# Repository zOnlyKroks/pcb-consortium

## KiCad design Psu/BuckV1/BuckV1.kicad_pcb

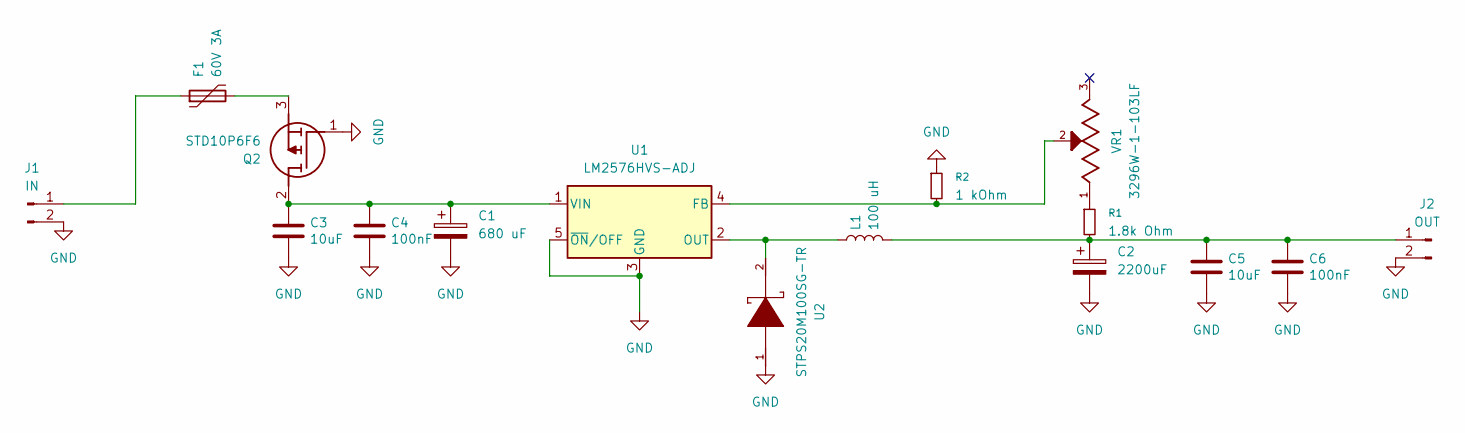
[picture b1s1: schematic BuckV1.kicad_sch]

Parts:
C1: 680 uF; CP_Radial_D12.5mm_P5.00mm; LCSC Part # C233101
C2: 2200uF; CP_Radial_D16.0mm_P7.50mm; LCSC Part # C49256808
C3, C5: 10uF; C_0603_1608Metric; LCSC C19702
C4, C6: 100nF; C_0603_1608Metric; LCSC C14663
F1: 60V 3A; Polyfuse_60R300XF; LCSC Part # C207120
J1: IN; PinHeader_1x02_P2.54mm_Vertical; LCSC Part # C492401
J2: OUT; PinHeader_1x02_P2.54mm_Vertical; LCSC Part # C492401
L1: 100 uH; L_12x12mm_H8mm; LCSC Part # C5368704
Q2: STD10P6F6; Mouser Part Number 511-STD10P6F6
R1: 1.8k Ohm; R_0805_2012Metric; LCSC Part # C17398
R2: 1 kOhm; R_0805_2012Metric; LCSC Part # C95781
U1: LM2576HVS-ADJ; TO-263-5_TabPin3; LCSC Part # C18212635
U2: STPS20M100SG-TR; MANUFACTURER_PART_NUMBER STPS20M100SGTR; LCSC Part # C969989
VR1: 3296W-1-103LF; TRIM_3296W-1-103LF; PARTREV 05/16; LCSC Part # C49190453

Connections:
GND: C1.2, C2.2, C3.2, C4.2, C5.2, C6.2, J1.2, J2.2, Q2.1 (G), R2.1, U1.3 (GND), U1.5 (~ON/OFF), U2.1
unnamed: F1.1, J1.1
unnamed: C2.1, C5.1, C6.1, J2.1, L1.2, R1.2
unnamed: C1.1, C3.1, C4.1, Q2.2 (D), U1.1 (VIN)
unnamed: F1.2, Q2.3 (S)
unnamed: R1.1, VR1.1
unnamed: R2.2, U1.4 (FB), VR1.2
unnamed: L1.1, U1.2 (OUT), U2.2

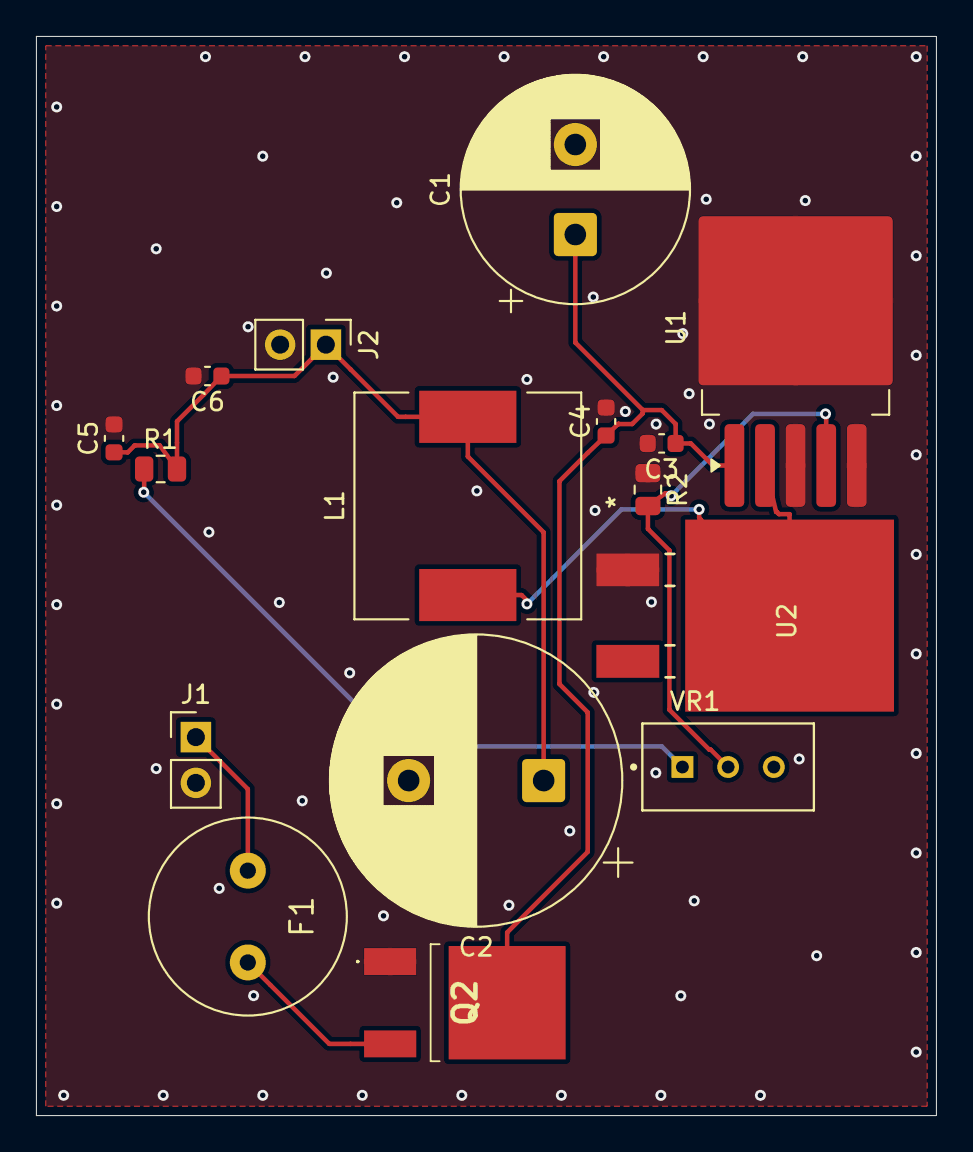
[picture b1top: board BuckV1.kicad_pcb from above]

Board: 2 copper layers, 50.0 x 59.9 mm, 16 parts (0 on the bottom side), 8 nets.

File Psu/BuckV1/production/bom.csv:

Designator,Footprint,Quantity,Value,LCSC Part #
C1,CP_Radial_D12.5mm_P5.00mm,1,680 uF,C233101
C2,CP_Radial_D16.0mm_P7.50mm,1,2200uF,C49256808
"C3, C5",0603,2,10uF,C19702
"C4, C6",0603,2,100nF,C14663
F1,Polyfuse_60R300XF,1,60V 3A,C207120
J1,PinHeader_1x02_P2.54mm_Vertical,1,IN,C492401
J2,PinHeader_1x02_P2.54mm_Vertical,1,OUT,C492401
L1,L_12x12mm_H8mm,1,100 uH,C5368704
Q2,STD10P6F6,1,STD10P6F6,C457501
R1,0805,1,1.8k Ohm,C17398
R2,0805,1,1 kOhm,C95781
U1,TO-263-5_TabPin3,1,LM2576HVS-ADJ,C18212635
U2,STPS20M100SG-TR,1,STPS20M100SG-TR,C969989
VR1,TRIM_3296W-1-103LF,1,3296W-1-103LF,C49190453

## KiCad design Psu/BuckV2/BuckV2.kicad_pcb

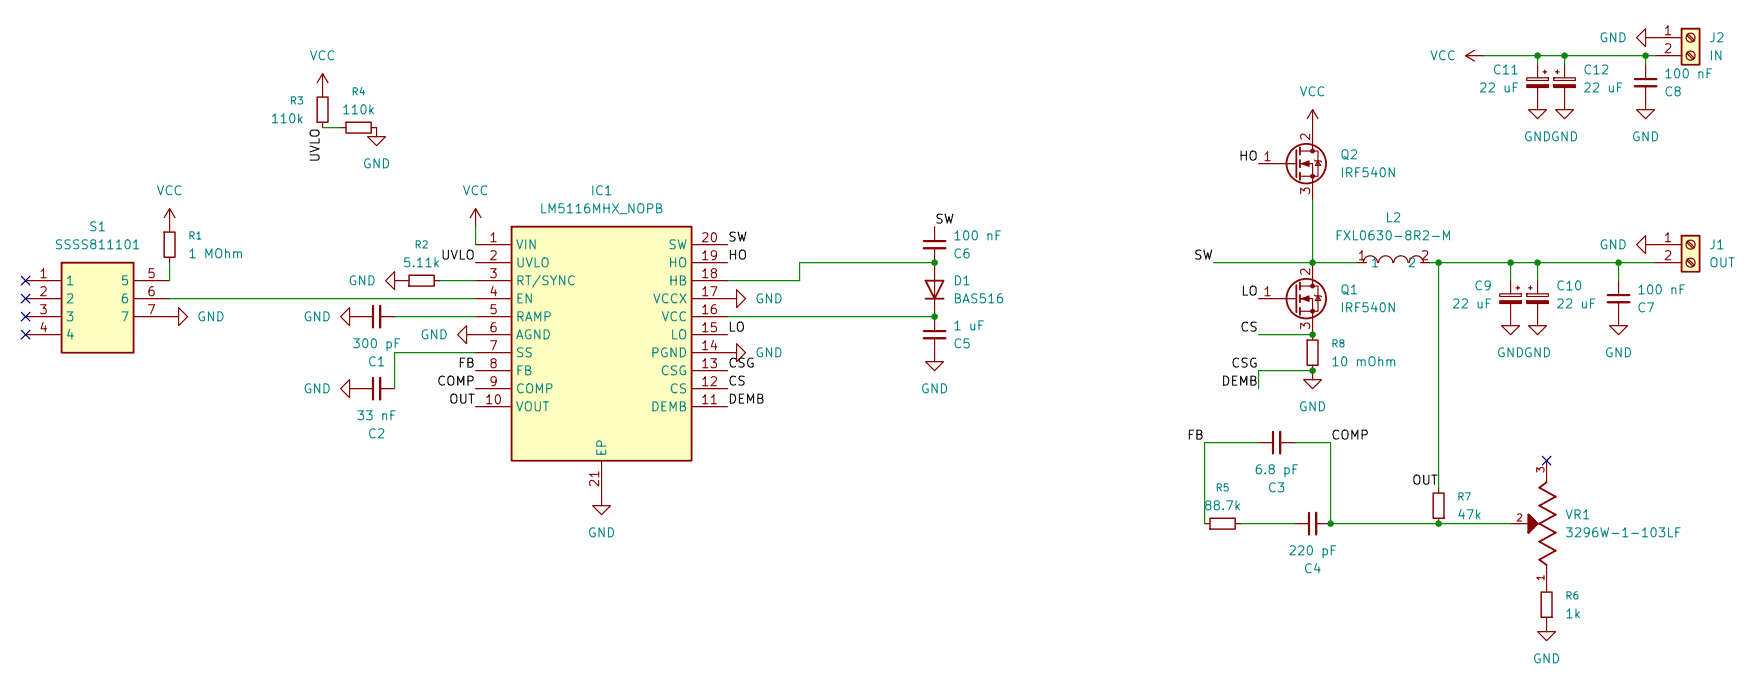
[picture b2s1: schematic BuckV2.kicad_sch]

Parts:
C1: 300 pF; C_0603_1608Metric
C2: 33 nF; C_0603_1608Metric
C3: 6.8 pF; C_0603_1608Metric
C4: 220 pF; C_0603_1608Metric
C5: 1 uF; C_0603_1608Metric
C6, C7, C8: 100 nF; C_0603_1608Metric
C9, C10, C11, C12: 22 uF; CP_Radial_D10.0mm_P5.00mm
D1: BAS516; D_SOD-523
IC1: LM5116MHX_NOPB; SOP65P640X110-21N; Mouser Part Number 926-LM5116MHX/NOPB
J1: OUT; WJ500V-5.08-2P
J2: IN; WJ500V-5.08-2P
L2: FXL0630-8R2-M; IND-SMD_L7.0-W6.6_FXL0630; MPN FXL0630-8R2-M; LCSC Part C167222
Q1, Q2: IRF540N; TO-220-3_Vertical
R1: 1 MOhm; R_0603_1608Metric
R2: 5.11k; R_0603_1608Metric
R3, R4: 110k; R_0603_1608Metric
R5: 88.7k; R_0603_1608Metric
R6: 1k; R_0603_1608Metric
R7: 47k; R_0603_1608Metric
R8: 10 mOhm; R_0603_1608Metric
S1: SSSS811101; Mouser Part Number 688-SSSS811101
VR1: 3296W-1-103LF; TRIM_3296W-1-103LF; PARTREV 05/16

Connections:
/COMP: C3.2, C4.2, IC1.9 (COMP), R7.1, VR1.2
/CS: IC1.12 (CS), Q1.3 (S), R8.1
/FB: C3.1, IC1.8 (FB), R5.1
/HO: IC1.19 (HO), Q2.1 (G)
/LO: IC1.15 (LO), Q1.1 (G)
/OUT: C7.1, C9.1, C10.1, IC1.10 (VOUT), J1.2, L2.2, R7.2
/SW: C6.1, IC1.20 (SW), L2.1, Q1.2 (D), Q2.3 (S)
/UVLO: IC1.2 (UVLO), R3.1, R4.1
GND: C1.1, C2.1, C5.2, C7.2, C8.2, C9.2, C10.2, C11.2, C12.2, IC1.6 (AGND), IC1.11 (DEMB), IC1.13 (CSG), IC1.14 (PGND), IC1.17 (VCCX), IC1.21 (EP), J1.1, J2.1, R2.1, R4.2, R6.1, R8.2, S1.7
unnamed: C4.1, R5.2
unnamed: C6.2, D1.2 (A), IC1.18 (HB)
unnamed: C5.1, D1.1 (K), IC1.16 (VCC)
unnamed: IC1.4 (EN), S1.6
unnamed: C1.2, IC1.5 (RAMP)
unnamed: IC1.3 (RT/SYNC), R2.2
unnamed: C2.2, IC1.7 (SS)
unnamed: R1.2, S1.5
unnamed: R6.2, VR1.1
VCC: C8.1, C11.1, C12.1, IC1.1 (VIN), J2.2, Q2.2 (D), R1.1, R3.2

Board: 2 copper layers, 29 parts (0 on the bottom side), 19 nets, no tracks yet.

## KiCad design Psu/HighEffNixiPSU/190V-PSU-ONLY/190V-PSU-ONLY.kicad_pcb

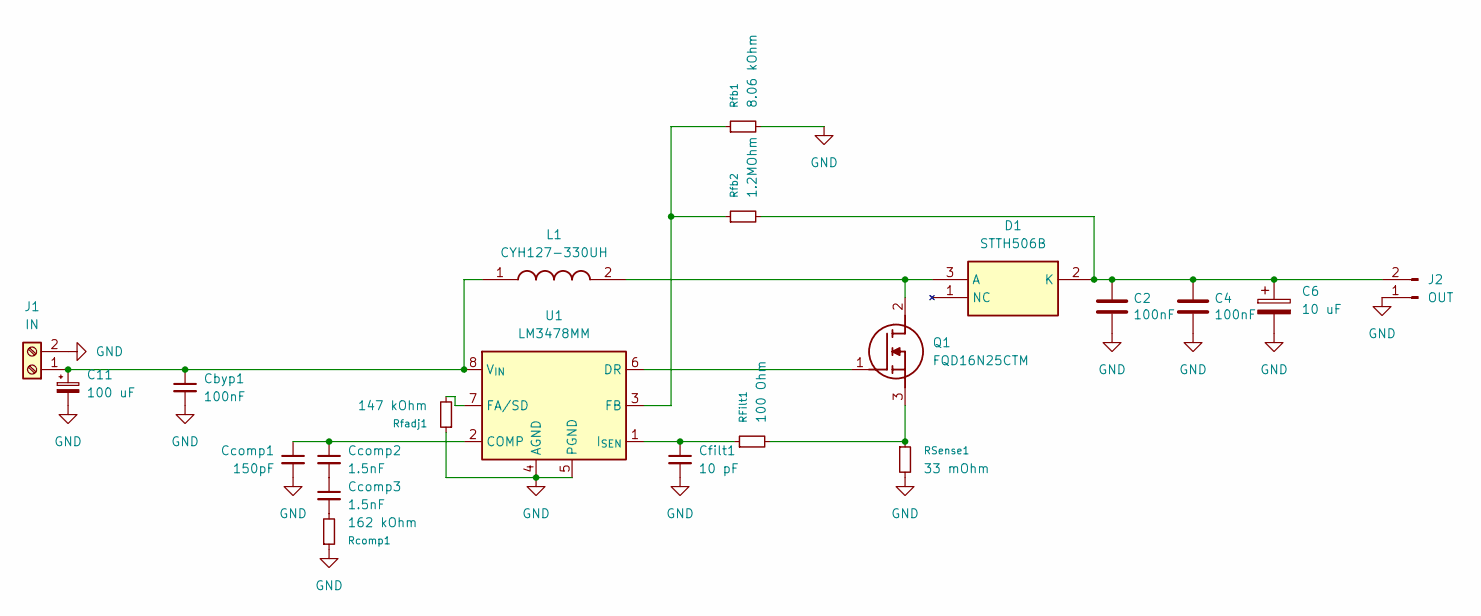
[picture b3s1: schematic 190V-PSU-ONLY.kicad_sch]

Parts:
C2, C4: 100nF; C_1206_3216Metric; LCSC C365814
C6: 10 uF; C_Elec_10x10.2; LCSC Part # C48970948
C11: 100 uF; CP_EIA-3216-18_Kemet-A
Cbyp1: 100nF; C_0805_2012Metric; LCSC Part # C28233
Ccomp1: 150pF; C_0805_2012Metric; LCSC Part # C1716
Ccomp2, Ccomp3: 1.5nF; C_0805_2012Metric; LCSC Part # C1717
Cfilt1: 10 pF; C_0805_2012Metric; LCSC Part # C107107
D1: STTH506B; STTH506BTR; Mouser Part Number 511-STTH506B-TR
J1: IN; WJ500V-5.08-2P
J2: OUT; PinHeader_1x02_P2.54mm_Horizontal
L1: CYH127-330UH; Mouser Part Number 652-SDR1307-331KL
Q1: FQD16N25CTM; Mouser Part Number 512-FQD16N25CTM
RFilt1: 100 Ohm; R_0805_2012Metric; LCSC Part # C17408
RSense1: 33 mOhm; R_1210_3225Metric; LCSC Part # C723419
Rcomp1: 162 kOhm; R_0805_2012Metric; LCSC Part # C47115899
Rfadj1: 147 kOhm; R_0805_2012Metric; LCSC Part # C47115874
Rfb1: 8.06 kOhm; R_0805_2012Metric; LCSC Part # C857074
Rfb2: 1.2MOhm; R_1206_3216Metric; LCSC Part # C36337
U1: LM3478MM; VSSOP-8_3x3mm_P0.65mm; LCSC Part # C9404

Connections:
GND: C2.2, C4.2, C6.2, C11.2, Cbyp1.2, Ccomp1.2, Cfilt1.2, J1.2, J2.1, RSense1.2, Rcomp1.1, Rfadj1.1, Rfb1.2, U1.4 (AGND), U1.5 (PGND)
unnamed: Ccomp2.2, Ccomp3.1
unnamed: Ccomp3.2, Rcomp1.2
unnamed: D1.3 (A), L1.2, Q1.2 (D)
unnamed: C2.1, C4.1, C6.1, D1.2 (K), J2.2, Rfb2.2
unnamed: C11.1, Cbyp1.1, J1.1, L1.1, U1.8 (V_{IN})
unnamed: Q1.1 (G), U1.6 (DR)
unnamed: Q1.3 (S), RFilt1.2, RSense1.1
unnamed: Ccomp1.1, Ccomp2.1, U1.2 (COMP)
unnamed: Rfadj1.2, U1.7 (FA/SD)
unnamed: Rfb1.1, Rfb2.1, U1.3 (FB)
unnamed: Cfilt1.1, RFilt1.1, U1.1 (I_{SEN})

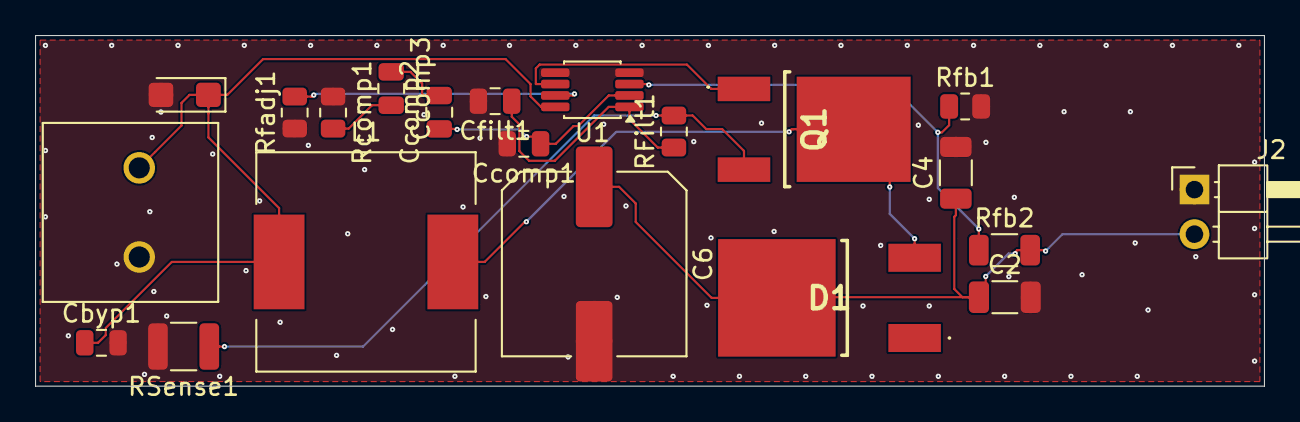
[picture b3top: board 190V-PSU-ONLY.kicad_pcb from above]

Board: 2 copper layers, 70.0 x 20.0 mm, 21 parts (0 on the bottom side), 12 nets.

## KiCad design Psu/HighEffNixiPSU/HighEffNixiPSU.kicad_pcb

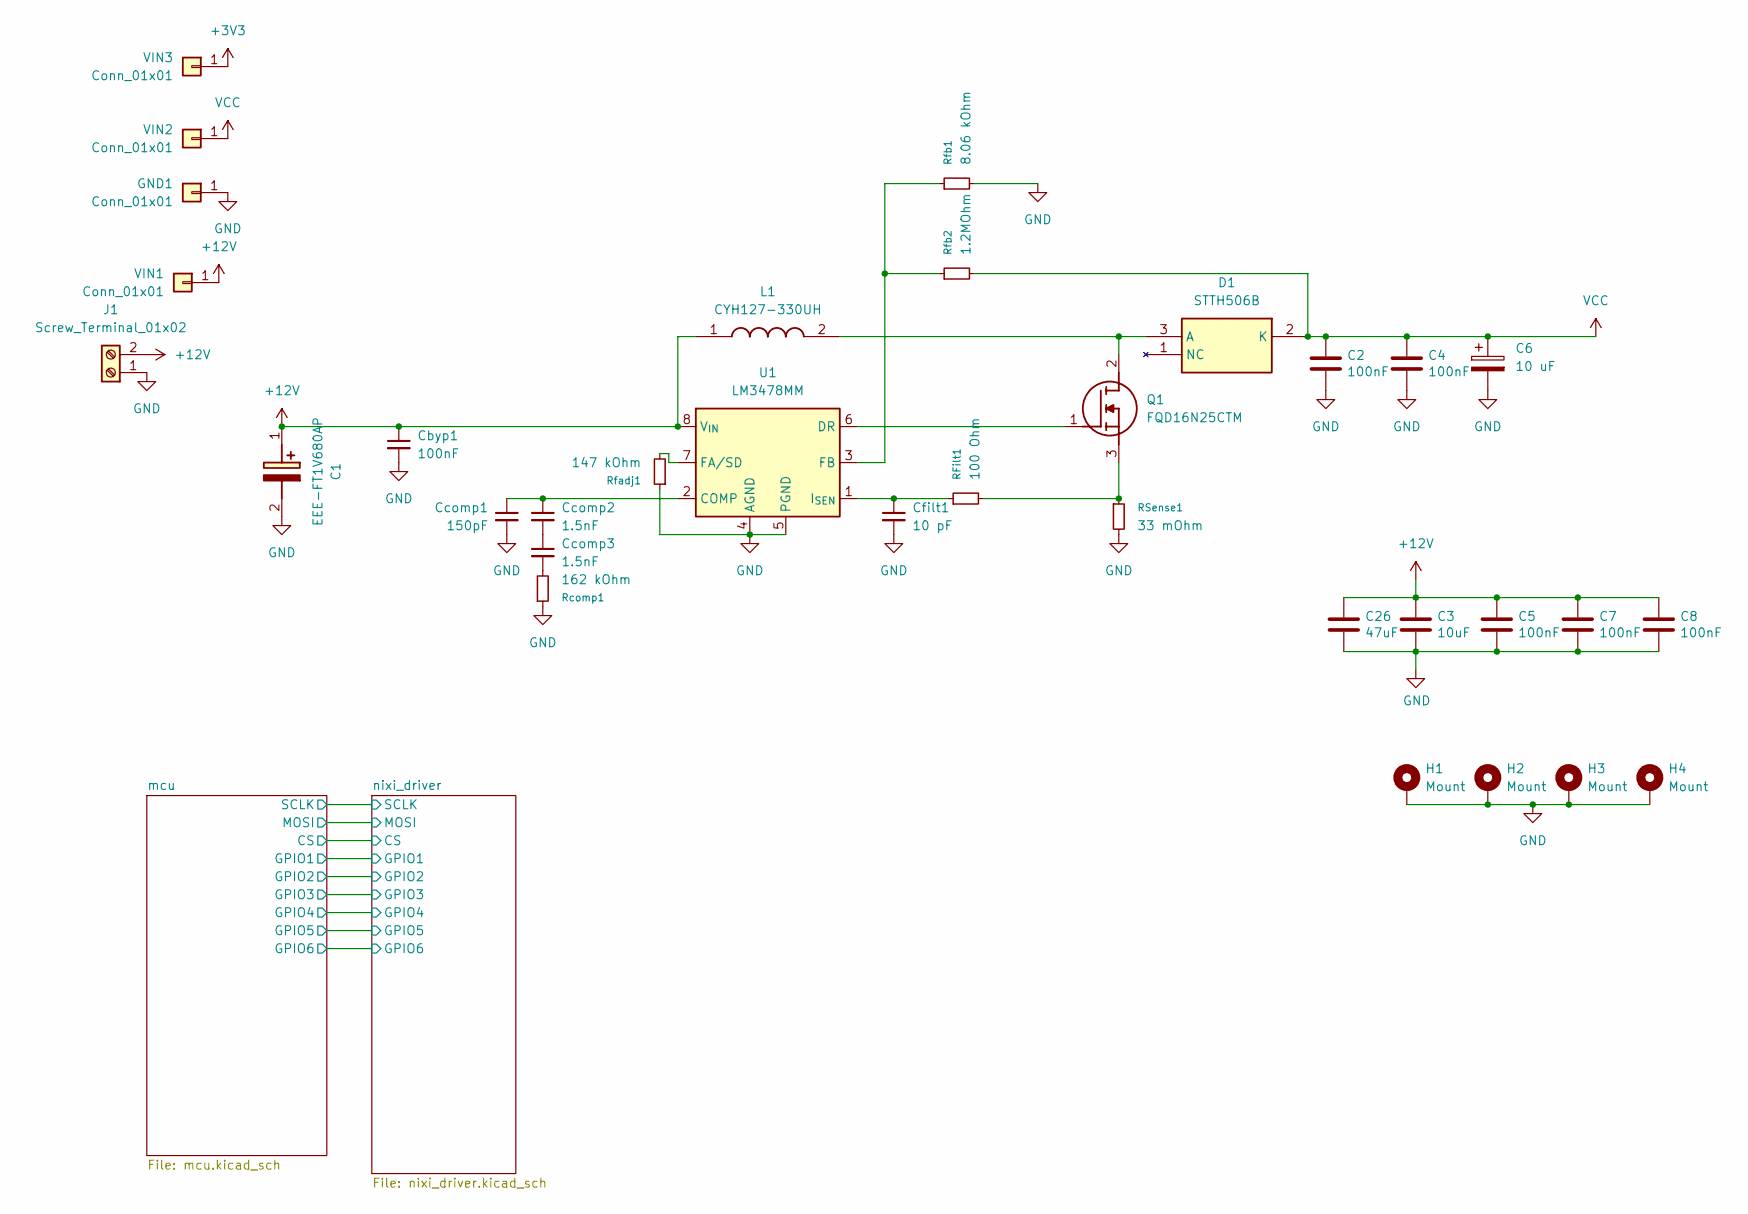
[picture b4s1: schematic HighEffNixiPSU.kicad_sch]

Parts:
C1: EEE-FT1V680AP; EEE1AA101SP; Mouser Part Number 667-EEE-FT1V680AP
C2, C4: 100nF; C_1206_3216Metric; LCSC C365814
C3: 10uF; C_0603_1608Metric; LCSC C1691
C5, C7, C8: 100nF; C_0603_1608Metric; LCSC C14663
C6: 10 uF; C_Elec_10x10.2; LCSC Part # C48970948
C26: 47uF; C_1206_3216Metric; LCSC C96123
Cbyp1: 100nF; C_0805_2012Metric; LCSC Part # C28233
Ccomp1: 150pF; C_0805_2012Metric; LCSC Part # C1716
Ccomp2, Ccomp3: 1.5nF; C_0805_2012Metric; LCSC Part # C1717
Cfilt1: 10 pF; C_0805_2012Metric; LCSC Part # C107107
D1: STTH506B; STTH506BTR; Mouser Part Number 511-STTH506B-TR
GND1: Conn_01x01; PinHeader_1x01_P2.54mm_Vertical; LCSC Part # C492400
H1, H2, H3, H4: Mount; MountingHole_3mm_Pad_TopOnly
J1: Screw_Terminal_01x02; WJ500V-5.08-2P
L1: CYH127-330UH; Mouser Part Number 652-SDR1307-331KL
Q1: FQD16N25CTM; Mouser Part Number 512-FQD16N25CTM
RFilt1: 100 Ohm; R_0805_2012Metric; LCSC Part # C17408
RSense1: 33 mOhm; R_1210_3225Metric; LCSC Part # C723419
Rcomp1: 162 kOhm; R_0805_2012Metric; LCSC Part # C47115899
Rfadj1: 147 kOhm; R_0805_2012Metric; LCSC Part # C47115874
Rfb1: 8.06 kOhm; R_0805_2012Metric; LCSC Part # C857074
Rfb2: 1.2MOhm; R_1206_3216Metric; LCSC Part # C36337
U1: LM3478MM; VSSOP-8_3x3mm_P0.65mm; LCSC Part # C9404
VIN1, VIN2, VIN3: Conn_01x01; PinHeader_1x01_P2.54mm_Vertical; LCSC Part # C492400

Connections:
+3V3: VIN3.1 (Pin_1_1); also elsewhere on the board
+12V: C1.1 (+), C3.1, C5.1, C7.1, C8.1, C26.1, Cbyp1.1, J1.2, L1.1, U1.8 (V_{IN}), VIN1.1 (Pin_1_1); also elsewhere on the board
GND: C1.2 (-), C2.2, C3.2, C4.2, C5.2, C6.2, C7.2, C8.2, C26.2, Cbyp1.2, Ccomp1.2, Cfilt1.2, GND1.1 (Pin_1_1), H1.1 (1_1), H2.1 (1_1), H3.1 (1_1), H4.1 (1_1), J1.1, RSense1.2, Rcomp1.1, Rfadj1.1, Rfb1.2, U1.4 (AGND), U1.5 (PGND); also elsewhere on the board
unnamed: Ccomp2.2, Ccomp3.1
unnamed: Ccomp3.2, Rcomp1.2
unnamed: D1.3 (A), L1.2, Q1.2 (D)
unnamed: Q1.1 (G), U1.6 (DR)
unnamed: Q1.3 (S), RFilt1.2, RSense1.1
unnamed: Ccomp1.1, Ccomp2.1, U1.2 (COMP)
unnamed: Rfadj1.2, U1.7 (FA/SD)
unnamed: Rfb1.1, Rfb2.1, U1.3 (FB)
unnamed: Cfilt1.1, RFilt1.1, U1.1 (I_{SEN})
VCC: C2.1, C4.1, C6.1, D1.2 (K), Rfb2.2, VIN2.1 (Pin_1_1); also elsewhere on the board

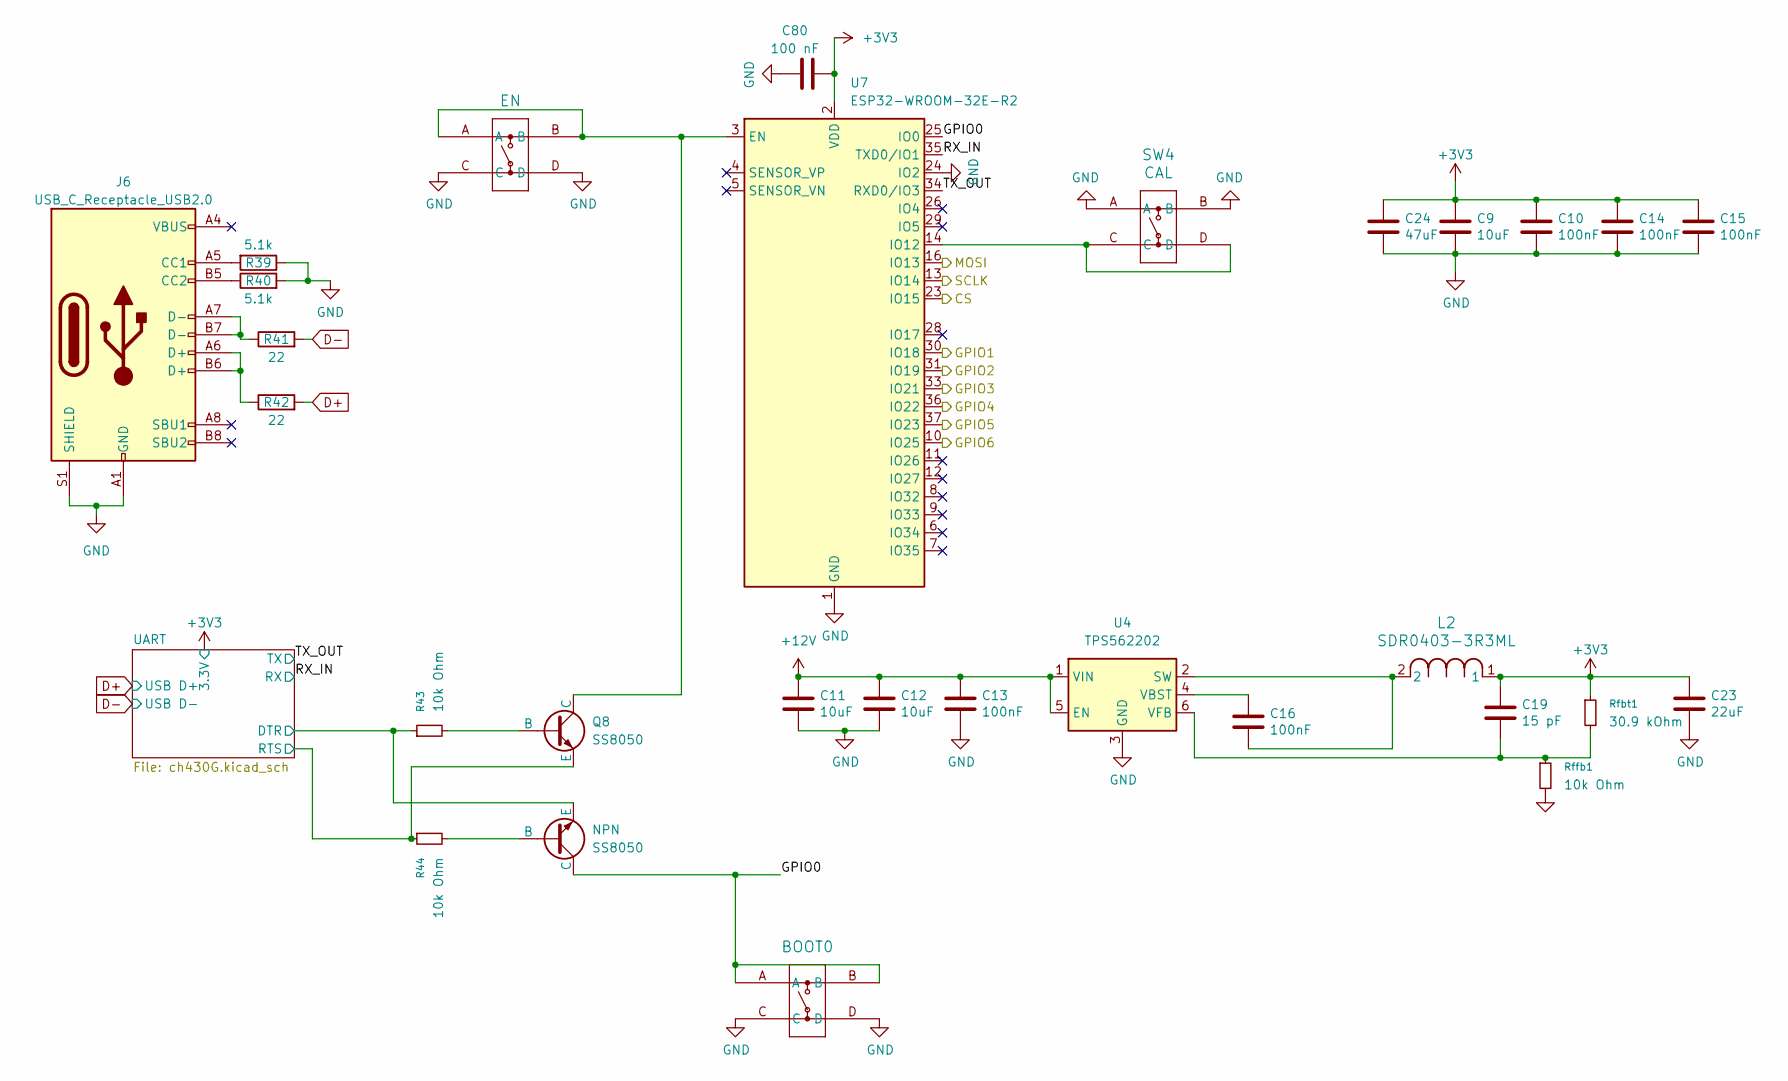
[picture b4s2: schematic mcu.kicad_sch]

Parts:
C9: 10uF; C_0603_1608Metric; LCSC C1691
C10, C13, C14, C15, C16: 100nF; C_0603_1608Metric; LCSC C14663
C11, C12: 10uF; C_0603_1608Metric; LCSC C92487
C19: 15 pF; R_0805_2012Metric; LCSC C107110
C23: 22uF; C_0805_2012Metric; LCSC C45783
C24: 47uF; C_1206_3216Metric; LCSC C96123
C80: 100 nF; C_0805_2012Metric; LCSC Part # C49678
J6: USB_C_Receptacle_USB2.0; USB_C_Receptacle_HRO_TYPE-C-31-M-12; JlcRotOffset 180
L2: SDR0403-3R3ML; IND_BOURNS_SDR0403; LCSC Part # C139481
Q8: SS8050; SOT-23; LCSC Part # C916392
R39, R40: 5.1k; R_0805_2012Metric; LCSC Part # C27834
R41, R42: 22; R_0805_2012Metric; LCSC Part # C17561
R43, R44: 10k Ohm; R_0805_2012Metric
Rfbt1: 30.9 kOhm; R_0603_1608Metric; LCSC Part # C2930090
Rffb1: 10k Ohm; R_0603_1608Metric; LCSC Part # C25804
SS8050: NPN; SOT-23; LCSC Part # C916392
SW3: EN; KH-6X6X5H-STM_SKE; LCSC Part # C2837531
SW4: CAL; KH-6X6X5H-STM_SKE; LCSC Part # C2837531
SW5: BOOT0; KH-6X6X5H-STM_SKE; LCSC Part # C2837531
U4: TPS562202; SOT-563; LCSC Part # C2877547
U7: ESP32-WROOM-32E-R2; ESP32-WROOM-32D

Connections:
+3V3: C9.1, C10.1, C14.1, C15.1, C19.1, C23.1, C24.1, C80.1, L2.1, Rfbt1.1, U7.2 (VDD); also elsewhere on the board
+12V: C11.1, C12.1, C13.1, U4.1 (VIN), U4.5 (EN); also elsewhere on the board
/mcu/CS: U7.23 (IO15); also elsewhere on the board
/mcu/GPIO0: SS8050.1 (C), SW5.A, SW5.B, U7.25 (IO0)
/mcu/GPIO1: U7.30 (IO18); also elsewhere on the board
/mcu/GPIO2: U7.31 (IO19); also elsewhere on the board
/mcu/GPIO3: U7.33 (IO21); also elsewhere on the board
/mcu/GPIO4: U7.36 (IO22); also elsewhere on the board
/mcu/GPIO5: U7.37 (IO23); also elsewhere on the board
/mcu/GPIO6: U7.10 (IO25); also elsewhere on the board
/mcu/MOSI: U7.16 (IO13); also elsewhere on the board
/mcu/RX_IN: U7.35 (TXD0/IO1); also elsewhere on the board
/mcu/SCLK: U7.13 (IO14); also elsewhere on the board
/mcu/TX_OUT: U7.34 (RXD0/IO3); also elsewhere on the board
/mcu/UART/DTR: R43.1, SS8050.3 (E); also elsewhere on the board
/mcu/UART/RTS: Q8.3 (E), R44.1; also elsewhere on the board
D+: R42.2; also elsewhere on the board
D-: R41.2; also elsewhere on the board
GND: C9.2, C10.2, C11.2, C12.2, C13.2, C14.2, C15.2, C23.2, C24.2, C80.2, J6.A1 (GND), J6.A12 (GND), J6.B1 (GND), J6.B12 (GND), J6.S1 (SHIELD), R39.1, R40.2, Rffb1.2, SW3.C, SW3.D, SW4.A, SW4.B, SW5.C, SW5.D, U4.3 (GND), U7.1 (GND), U7.15 (GND), U7.24 (IO2), U7.38 (GND), U7.39 (GND); also elsewhere on the board
unnamed: J6.A5 (CC1), R39.2
unnamed: J6.B5 (CC2), R40.1
unnamed: J6.A6 (D+), J6.B6 (D+), R42.1
unnamed: J6.A7 (D-), J6.B7 (D-), R41.1
unnamed: Q8.2 (B), R43.2
unnamed: Q8.1 (C), SW3.A, SW3.B, U7.3 (EN)
unnamed: R44.2, SS8050.2 (B)
unnamed: C16.2, L2.2, U4.2 (SW)
unnamed: C16.1, U4.4 (VBST)
unnamed: C19.2, Rfbt1.2, Rffb1.1, U4.6 (VFB)
unnamed: SW4.C, SW4.D, U7.14 (IO12)

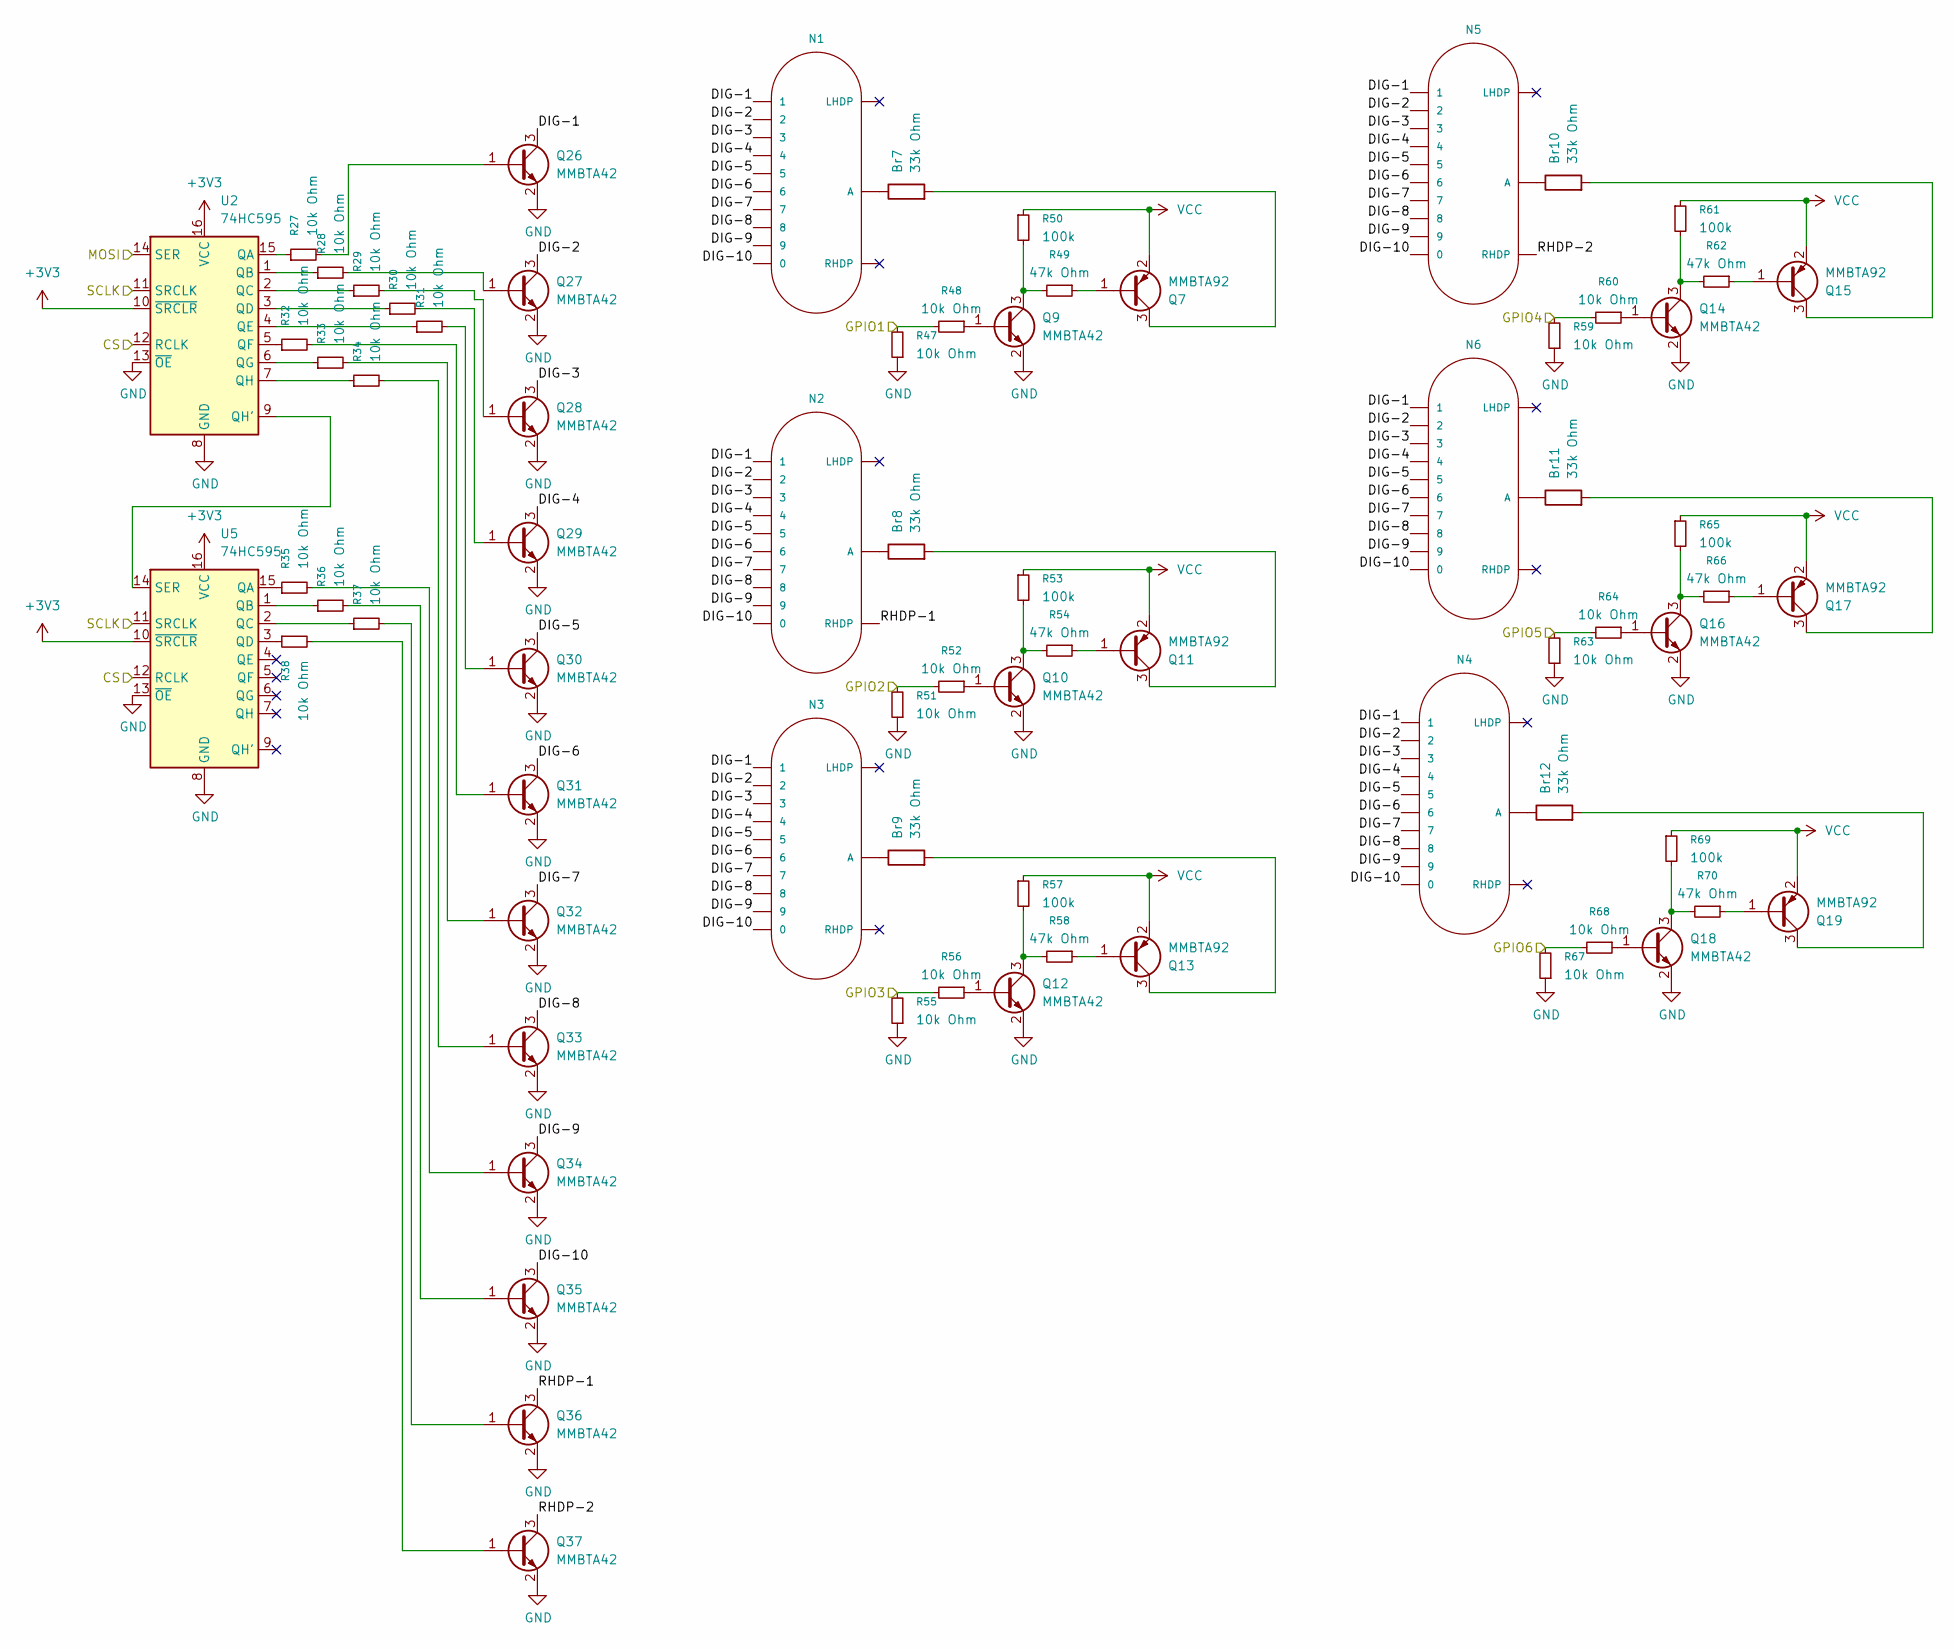
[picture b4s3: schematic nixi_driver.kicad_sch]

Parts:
Br7, Br8, Br9, Br10, Br11, Br12: 33k Ohm; R_0805_2012Metric; LCSC Part # C17633
N1, N2, N3, N4, N5, N6: IN-16; nixies-us-IN-16
Q7, Q11, Q13, Q15, Q17, Q19: MMBTA92; SOT-23
Q9, Q10, Q12, Q14, Q16, Q18, Q26, Q27, Q28, Q29, Q30, Q31, Q32, Q33, Q34, Q35, Q36, Q37: MMBTA42; SOT-23
R27, R28, R29, R30, R31, R32, R33, R34, R35, R36, R37, R38, R47, R48, R51, R52, R55, R56, R59, R60, R63, R64, R67, R68: 10k Ohm; R_0603_1608Metric; LCSC Part # C25804
R49, R54, R58, R62, R66, R70: 47k Ohm; R_0603_1608Metric; LCSC Part # C25804
R50, R53, R57, R61, R65, R69: 100k; R_0603_1608Metric; LCSC Part # C25804
U2, U5: 74HC595; SOIC-16_3.9x9.9mm_P1.27mm; LCSC Part # C10092

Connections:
+3V3: U2.10 (~SRCLR), U2.16 (VCC), U5.10 (~SRCLR), U5.16 (VCC); also elsewhere on the board
/mcu/CS: U2.12 (RCLK), U5.12 (RCLK); also elsewhere on the board
/mcu/GPIO1: R47.2, R48.2; also elsewhere on the board
/mcu/GPIO2: R51.2, R52.2; also elsewhere on the board
/mcu/GPIO3: R55.2, R56.2; also elsewhere on the board
/mcu/GPIO4: R59.2, R60.2; also elsewhere on the board
/mcu/GPIO5: R63.2, R64.2; also elsewhere on the board
/mcu/GPIO6: R67.2, R68.2; also elsewhere on the board
/mcu/MOSI: U2.14 (SER); also elsewhere on the board
/mcu/SCLK: U2.11 (SRCLK), U5.11 (SRCLK); also elsewhere on the board
/nixi_driver/DIG-1: N1.1, N2.1, N3.1, N4.1, N5.1, N6.1, Q26.3 (C)
/nixi_driver/DIG-2: N1.2, N2.2, N3.2, N4.2, N5.2, N6.2, Q27.3 (C)
/nixi_driver/DIG-3: N1.3, N2.3, N3.3, N4.3, N5.3, N6.3, Q28.3 (C)
/nixi_driver/DIG-4: N1.4, N2.4, N3.4, N4.4, N5.4, N6.4, Q29.3 (C)
/nixi_driver/DIG-5: N1.5, N2.5, N3.5, N4.5, N5.5, N6.5, Q30.3 (C)
/nixi_driver/DIG-6: N1.6, N2.6, N3.6, N4.6, N5.6, N6.6, Q31.3 (C)
/nixi_driver/DIG-7: N1.7, N2.7, N3.7, N4.7, N5.7, N6.7, Q32.3 (C)
/nixi_driver/DIG-8: N1.8, N2.8, N3.8, N4.8, N5.8, N6.8, Q33.3 (C)
/nixi_driver/DIG-9: N1.9, N2.9, N3.9, N4.9, N5.9, N6.9, Q34.3 (C)
/nixi_driver/DIG-10: N1.0, N2.0, N3.0, N4.0, N5.0, N6.0, Q35.3 (C)
/nixi_driver/RHDP-1: N2.RHDP, Q36.3 (C)
/nixi_driver/RHDP-2: N5.RHDP, Q37.3 (C)
GND: Q9.2 (E), Q10.2 (E), Q12.2 (E), Q14.2 (E), Q16.2 (E), Q18.2 (E), Q26.2 (E), Q27.2 (E), Q28.2 (E), Q29.2 (E), Q30.2 (E), Q31.2 (E), Q32.2 (E), Q33.2 (E), Q34.2 (E), Q35.2 (E), Q36.2 (E), Q37.2 (E), R47.1, R51.1, R55.1, R59.1, R63.1, R67.1, U2.8 (GND), U2.13 (~OE), U5.8 (GND), U5.13 (~OE); also elsewhere on the board
unnamed: Br7.1, N1.A
unnamed: Br8.1, N2.A
unnamed: Br9.1, N3.A
unnamed: Br10.1, N5.A
unnamed: Br11.1, N6.A
unnamed: Br12.1, N4.A
unnamed: Q7.1 (B), R49.1
unnamed: Br7.2, Q7.3 (C)
unnamed: Q9.1 (B), R48.1
unnamed: Q9.3 (C), R49.2, R50.2
unnamed: Q10.1 (B), R52.1
unnamed: Q10.3 (C), R53.2, R54.2
unnamed: Q11.1 (B), R54.1
unnamed: Br8.2, Q11.3 (C)
unnamed: Q12.1 (B), R56.1
unnamed: Q12.3 (C), R57.2, R58.2
unnamed: Q13.1 (B), R58.1
unnamed: Br9.2, Q13.3 (C)
unnamed: Q14.1 (B), R60.1
unnamed: Q14.3 (C), R61.2, R62.2
unnamed: Q15.1 (B), R62.1
unnamed: Br10.2, Q15.3 (C)
unnamed: Q16.1 (B), R64.1
unnamed: Q16.3 (C), R65.2, R66.2
unnamed: Q17.1 (B), R66.1
unnamed: Br11.2, Q17.3 (C)
unnamed: Q18.1 (B), R68.1
unnamed: Q18.3 (C), R69.2, R70.2
unnamed: Q19.1 (B), R70.1
unnamed: Br12.2, Q19.3 (C)
unnamed: Q26.1 (B), R27.2
unnamed: Q27.1 (B), R28.2
unnamed: Q28.1 (B), R29.2
unnamed: Q29.1 (B), R30.2
unnamed: Q30.1 (B), R31.2
unnamed: Q31.1 (B), R32.2
unnamed: Q32.1 (B), R33.2
unnamed: Q33.1 (B), R34.2
unnamed: Q34.1 (B), R35.2
unnamed: Q35.1 (B), R36.2
unnamed: Q36.1 (B), R37.2
unnamed: Q37.1 (B), R38.2
unnamed: R27.1, U2.15 (QA)
unnamed: R28.1, U2.1 (QB)
unnamed: R29.1, U2.2 (QC)
unnamed: R30.1, U2.3 (QD)
unnamed: R31.1, U2.4 (QE)
unnamed: R32.1, U2.5 (QF)
unnamed: R33.1, U2.6 (QG)
unnamed: U2.9 (QH'), U5.14 (SER)
unnamed: R34.1, U2.7 (QH)
unnamed: R35.1, U5.15 (QA)
unnamed: R36.1, U5.1 (QB)
unnamed: R37.1, U5.2 (QC)
unnamed: R38.1, U5.3 (QD)
VCC: Q7.2 (E), Q11.2 (E), Q13.2 (E), Q15.2 (E), Q17.2 (E), Q19.2 (E), R50.1, R53.1, R57.1, R61.1, R65.1, R69.1; also elsewhere on the board

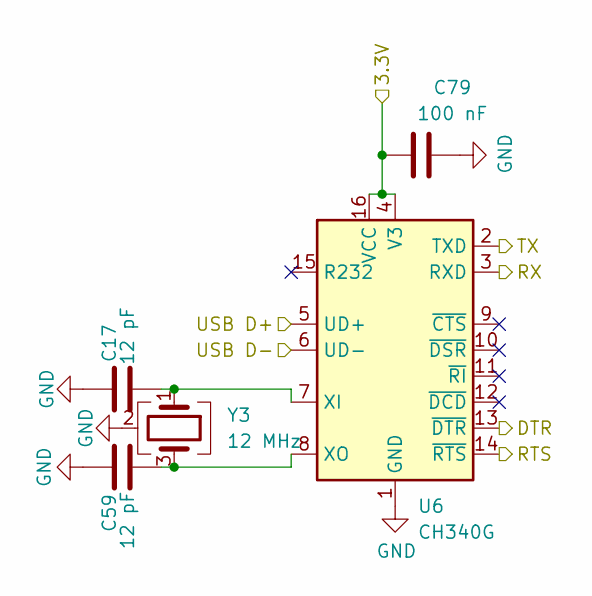
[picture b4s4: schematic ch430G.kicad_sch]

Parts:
C17, C59: 12 pF; C_0805_2012Metric; LCSC Part # C1792
C79: 100 nF; C_0805_2012Metric; LCSC Part # C49678
U6: CH340G; SOIC-16_3.9x9.9mm_P1.27mm
Y3: 12 MHz; Crystal_SMD_3225-4Pin_3.2x2.5mm; LCSC Part # C19631429

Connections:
+3V3: C79.2, U6.4 (V3), U6.16 (VCC); also elsewhere on the board
/mcu/RX_IN: U6.3 (RXD); also elsewhere on the board
/mcu/TX_OUT: U6.2 (TXD); also elsewhere on the board
/mcu/UART/DTR: U6.13 (~DTR); also elsewhere on the board
/mcu/UART/RTS: U6.14 (~RTS); also elsewhere on the board
D+: U6.5 (UD+); also elsewhere on the board
D-: U6.6 (UD-); also elsewhere on the board
GND: C17.1, C59.1, C79.1, U6.1 (GND), Y3.2 (G), Y3.4 (G); also elsewhere on the board
unnamed: C17.2, U6.7 (XI), Y3.1
unnamed: C59.2, U6.8 (XO), Y3.3
